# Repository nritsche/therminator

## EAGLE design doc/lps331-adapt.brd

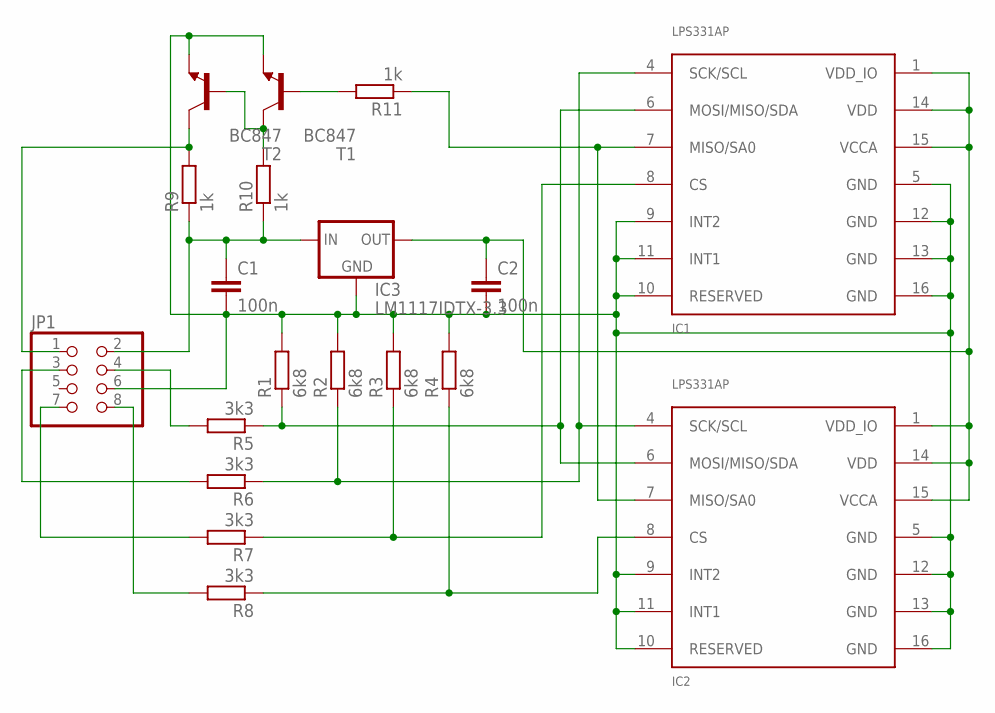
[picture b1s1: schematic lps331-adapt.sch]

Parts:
C1, C2: 100n; C1206
IC1, IC2: LPS331AP; HCLGA-16L
IC3: LM1117IDTX-3.3; TO252
JP1: PINHD-2X4; 2X04
R1, R2, R3, R4: 6k8; R1206
R5, R6, R7, R8: 3k3; R1206
R9, R10, R11: 1k; R1206
T1, T2: BC847; SOT23

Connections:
+3.3V: C2.1, IC1.1 (VDD_IO), IC1.14 (VDD), IC1.15 (VCCA), IC2.1 (VDD_IO), IC2.14 (VDD), IC2.15 (VCCA), IC3.TAB (OUT)
+5V: C1.1, IC3.2 (IN), JP1.2, R9.1, R10.1
GND: C1.2, C2.2, IC1.5 (GND), IC1.9 (INT2), IC1.10 (RESERVED), IC1.11 (INT1), IC1.12 (GND), IC1.13 (GND), IC1.16 (GND), IC2.5 (GND), IC2.9 (INT2), IC2.10 (RESERVED), IC2.11 (INT1), IC2.12 (GND), IC2.13 (GND), IC2.16 (GND), IC3.1 (GND), JP1.6, R1.2, R2.2, R3.2, R4.2, T1.2 (E), T2.2 (E)
unnamed: IC1.6 (MOSI/MISO/SDA), IC2.6 (MOSI/MISO/SDA), R1.1, R5.1
unnamed: IC1.7 (MISO/SA0), IC2.7 (MISO/SA0), R11.1
unnamed: JP1.4, R5.2
unnamed: JP1.3, R6.2
unnamed: JP1.7, R7.2
unnamed: JP1.8, R8.2
unnamed: IC1.4 (SCK/SCL), IC2.4 (SCK/SCL), R2.1, R6.1
unnamed: IC1.8 (CS), R3.1, R7.1
unnamed: IC2.8 (CS), R4.1, R8.1
unnamed: R10.2, T1.3 (C), T2.1 (B)
unnamed: JP1.1, R9.2, T2.3 (C)
unnamed: R11.2, T1.1 (B)

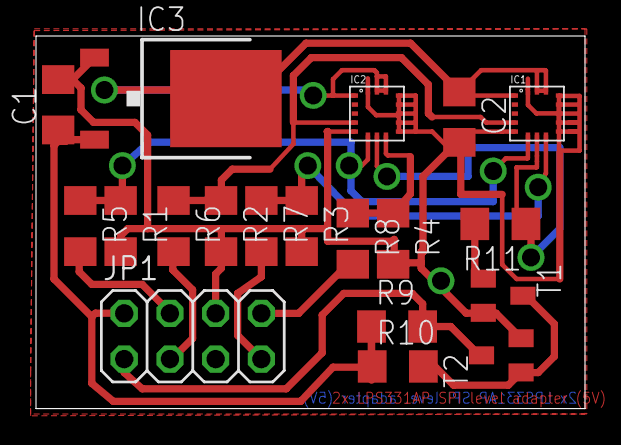
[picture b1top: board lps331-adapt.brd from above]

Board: 2 copper layers, 30.5 x 20.7 mm, 19 parts (0 on the bottom side), 15 nets.

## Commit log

2012-12-12 Makefile
2012-12-13 kk2multicopter and NextCopter in doc
2012-12-13 rm swp
2012-12-13 LCD says hello
2012-12-14 spi send
2012-12-14 cs pins
2012-12-14 no boolean aaaah
2012-12-14 baro
2012-12-14 warnings
2012-12-14 mega234p definitions
2012-12-14 first pressure read impl
2012-12-14 HAHA
2012-12-14 get_pressure
2012-12-14 pressure read
2012-12-14 fehlersuche
2012-12-15 i am BB
2012-12-15 doesnt work
2012-12-15 koa ahnung
2012-12-15 fixed warnings, baro.c, spi.c, testing output
2012-12-15 added missing init_baro() call and some other small fixes
2012-12-15 debugging
2012-12-15 fix baro.c send()
2012-12-16 gyro and accelerometer reading with test output
2012-12-16 sensors have to be tested, so let's play a bit pong ;)
2012-12-28 added blueRC-lib and testing connection to receiver
